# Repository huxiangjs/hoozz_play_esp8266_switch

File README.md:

# Hoozz Play ESP8266 Switch

Various switches

## Switch List

### (1) Simple Switch

### (2) TODO

## ESP8266_RTOS_SDK Version
```shell
$ git branch
* release/v3.3

$ git log --oneline | head -n 3
2bc42667 Merge branch 'bugfix/constrain_cryptography_v3.3' into 'release/v3.3'
4cab385e Tools: Constrain the cryptography package for avoiding breaking changes
6c438bce Merge branch 'bugfix/queue_arith_overflow_v3.3' into 'release/v3.3'

Toolchain version: crosstool-ng-1.22.0-100-ge567ec7b
Compiler version: 5.2.0
```

## Pull source code
```shell
git clone https://github.com/huxiangjs/hoozz_play_esp8266_switch.git --recurse-submodules
```

## Build and Flash

* first step: open the sdkconfig file, modify `CONFIG_ESPTOOLPY_PORT` to your serial.

```shell
cd hoozz_play_esp8266_switch/MCU
make -j$(nproc)
make flash
make monitor    # Monitor UART log output
```

## You can also directly burn the released bin file

1. Download the latest release zip package from the Releases column
2. Unzip the zip and you will see the following files:
   ```
   $ tree
   .
   |-- bootloader
   |   `-- bootloader.bin
   |-- partitions.bin
   `-- switch.bin

   1 directory, 3 files
   ```
3. Open the latest official download tool `flash_download_tool` (official download address: [other-tools](https://www.espressif.com/en/support/download/other-tools))
4. Use the following options: (1) `Chip Type [ESP8266]`; (2) `WorkMode [Develop]`; (3) `LoadMode [UART]`;
5. Set the burn parameters according to the following table:

   |    Parameters  |     Value   |
   | :------------: | :---------: |
   | bootloader.bin | 0x0000      |
   | switch.bin     | 0x10000     |
   | partitions.bin | 0x8000      |
   | SPI SPEED      | 40MHz       |
   | SPI MODE       | DIO         |
   | DoNotChgBin    | √           |
   | COM            | (Your port) |
   | BAUD           | 115200      |

6. Finally click **Start** to burn

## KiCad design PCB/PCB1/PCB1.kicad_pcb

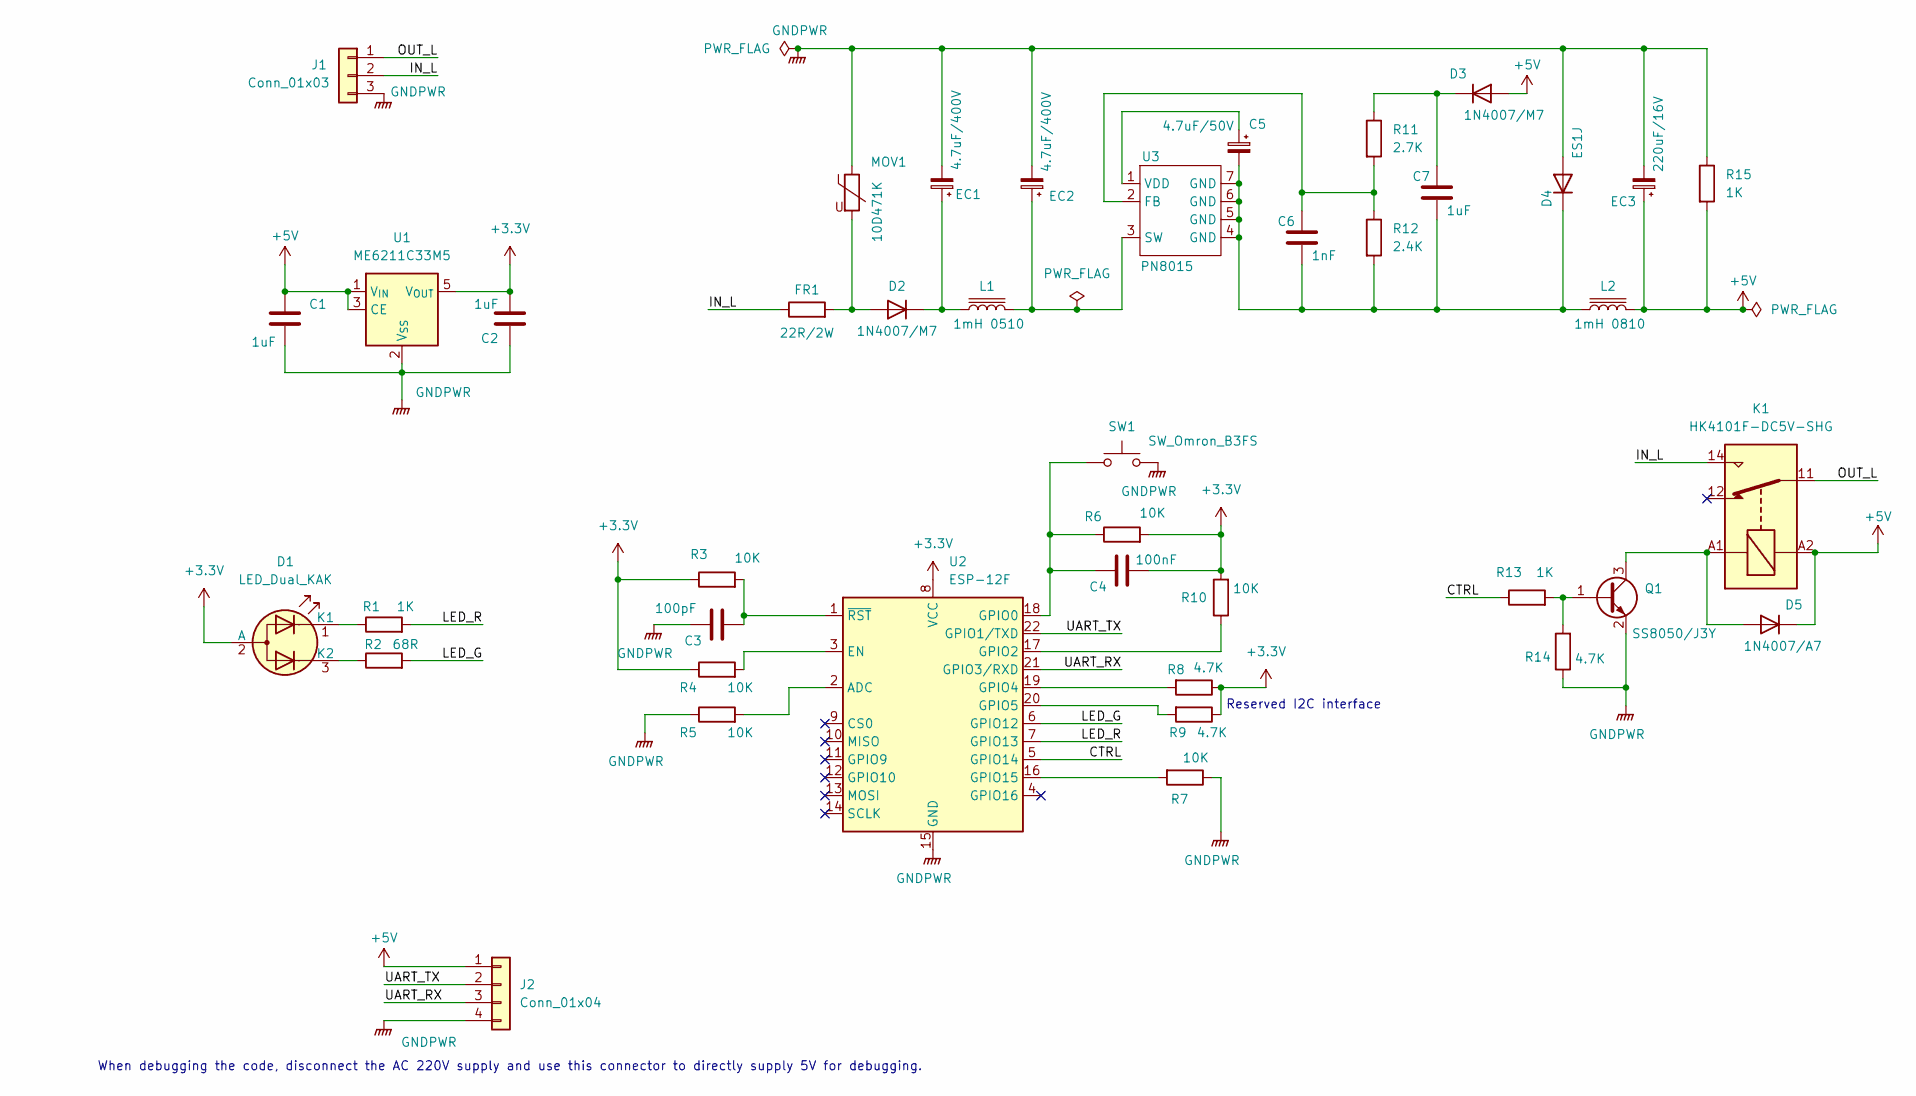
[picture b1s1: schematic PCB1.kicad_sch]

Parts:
C1, C2, C7: 1uF; C_0603_1608Metric
C3: 100pF; C_0603_1608Metric
C4: 100nF; C_0603_1608Metric
C5: 4.7uF/50V; CP_Radial_D4.0mm_P2.00mm
C6: 1nF; C_0603_1608Metric
D1: LED_Dual_KAK; LED_LiteOn_LTST-S326
D2, D3: 1N4007/M7; D_SMA
D4: ES1J; D_SMA
D5: 1N4007/A7; D_SOD-123F
EC1, EC2: 4.7uF/400V; CP_Radial_D8.0mm_P3.50mm
EC3: 220uF/16V; CP_Radial_D6.3mm_P2.50mm
FR1: 22R/2W; R_Axial_DIN0614_L14.3mm_D5.7mm_P15.24mm_Horizontal
J1: Conn_01x03; PhoenixContact_MCV_1,5_3-G-5.08_1x03_P5.08mm_Vertical
J2: Conn_01x04; PinHeader_1x04_P1.27mm_Vertical
K1: HK4101F-DC5V-SHG; Relay_HK4101F-DC5V-SHG
L1: 1mH 0510; L_Axial_L14.0mm_D4.5mm_P5.08mm_Vertical_Fastron_LACC
L2: 1mH 0810; L_Radial_D8.7mm_P5.00mm_Fastron_07HCP
MOV1: 10D471K; RV_Disc_D12mm_W4.5mm_P7.5mm
Q1: SS8050/J3Y; SOT-23
R1, R13, R15: 1K; R_0603_1608Metric
R2: 68R; R_0603_1608Metric
R3, R4, R5, R6, R7, R10: 10K; R_0603_1608Metric
R8, R9, R14: 4.7K; R_0603_1608Metric
R11: 2.7K; R_0603_1608Metric
R12: 2.4K; R_0603_1608Metric
SW1: SW_Omron_B3FS; SW_SPST_Omron_B3FS-100xP
U1: ME6211C33M5; SOT-23-5
U2: ESP-12F; ESP-12E
U3: PN8015; SOP-7_4.9x6mm_P1.27mm

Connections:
+3.3V: C2.2, C4.2, D1.2 (A), R3.1, R4.1, R6.2, R8.1, R9.1, R10.2, U1.5 (V_{OUT}), U2.8 (VCC)
+5V: C1.1, D3.2 (A), D5.1 (K), EC3.1, J2.1, K1.A2, L2.2, R15.2, U1.1 (V_{IN}), U1.3 (CE)
/CTRL: R13.1, U2.5 (GPIO14)
/IN_L: FR1.1, J1.2, K1.14
/LED_G: R2.2, U2.6 (GPIO12)
/LED_R: R1.2, U2.7 (GPIO13)
/OUT_L: J1.1, K1.11
/UART_RX: J2.3, U2.21 (GPIO3/RXD)
/UART_TX: J2.2, U2.22 (GPIO1/TXD)
GNDPWR: C1.2, C2.1, C3.1, D4.2 (A), EC1.2, EC2.2, EC3.2, J1.3, J2.4, MOV1.1, Q1.2 (E), R5.1, R7.1, R14.1, R15.1, SW1.2, U1.2 (V_{SS}), U2.15 (GND)
unnamed: D1.1 (K1), R1.1
unnamed: D1.3 (K2), R2.1
unnamed: D2.2 (A), FR1.2, MOV1.2
unnamed: D2.1 (K), EC1.1, L1.1
unnamed: C7.1, D3.1 (K), R11.1
unnamed: C5.2, C6.2, C7.2, D4.1 (K), L2.1, R12.2, U3.4 (GND), U3.5 (GND), U3.6 (GND), U3.7 (GND)
unnamed: D5.2 (A), K1.A1, Q1.3 (C)
unnamed: Q1.1 (B), R13.2, R14.2
unnamed: R5.2, U2.2 (ADC)
unnamed: R4.2, U2.3 (EN)
unnamed: C4.1, R6.1, SW1.1, U2.18 (GPIO0)
unnamed: R10.1, U2.17 (GPIO2)
unnamed: R8.2, U2.19 (GPIO4)
unnamed: R9.2, U2.20 (GPIO5)
unnamed: R7.2, U2.16 (GPIO15)
unnamed: C3.2, R3.2, U2.1 (~RST)
unnamed: C6.1, R11.2, R12.1, U3.2 (FB)
unnamed: EC2.1, L1.2, U3.3 (SW)
unnamed: C5.1, U3.1 (VDD)

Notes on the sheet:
When debugging the code, disconnect the AC 220V supply and use this connector to directly supply 5V for debugging.
Reserved I2C interface

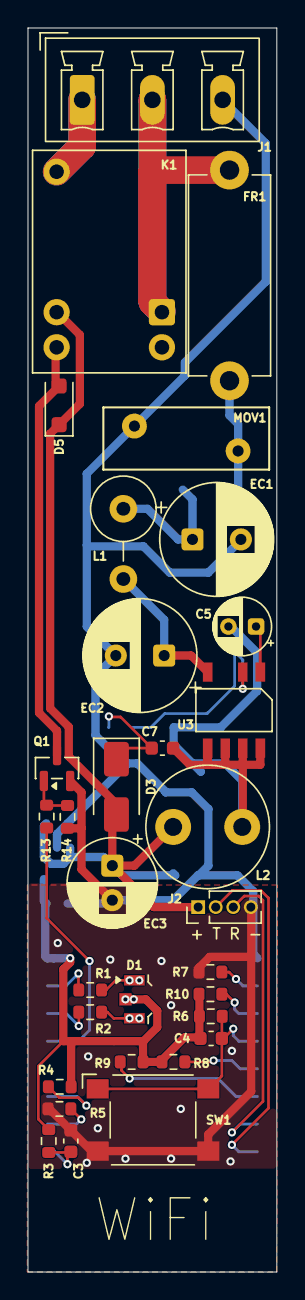
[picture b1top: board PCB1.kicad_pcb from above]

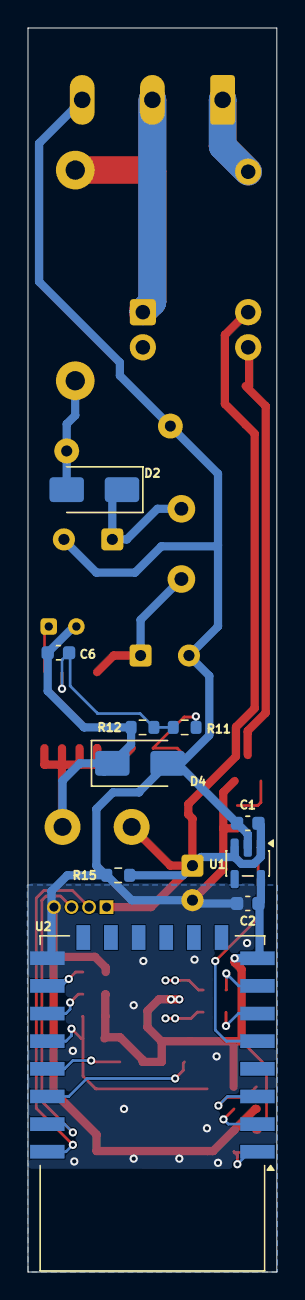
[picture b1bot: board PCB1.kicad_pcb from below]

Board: 2 copper layers, 18.0 x 90.0 mm, 42 parts (10 on the bottom side), 29 nets.
